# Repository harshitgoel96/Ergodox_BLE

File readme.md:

# There is no active development on this keyboard. Feel free to do whatever you want. I have moved to Pteron36.
The PCB is in working statue, but no further support or development will be done on this project.
------------------------------------------------------------------------------------------------------------------------------------------
Ergodox BLE
===========

I love my [Ergodox](https://i.imgur.com/aIGm8G6h.jpg) , but it is not Bluetooth. I recently got to know about Bluemicro from u/jpconstantineau which is replacement for pro micro with BLE built in, and I also got to know about Proton C, which has USB C connector and is built for QMK. The original Ergodox uses Tinsy and Ergodone uses pro micro. Both the PCBs don't have support for either of the MCU directly and so I got to work and redid the PCB and I came up with this.

This is my first attempt at making a PCB and I need help from PCB hardware experts if everything is ok or do I need make some changes.

The Ergodox Keyboard was originally developed by “Dox” (Dominic Beauchamp). 

------------------------------------------------------------------------------------------------------------------------------------------
There has ben lot of progress, the complete timeline of the project is available in [Project update](./project_udpate.md) file

First prototype assembled

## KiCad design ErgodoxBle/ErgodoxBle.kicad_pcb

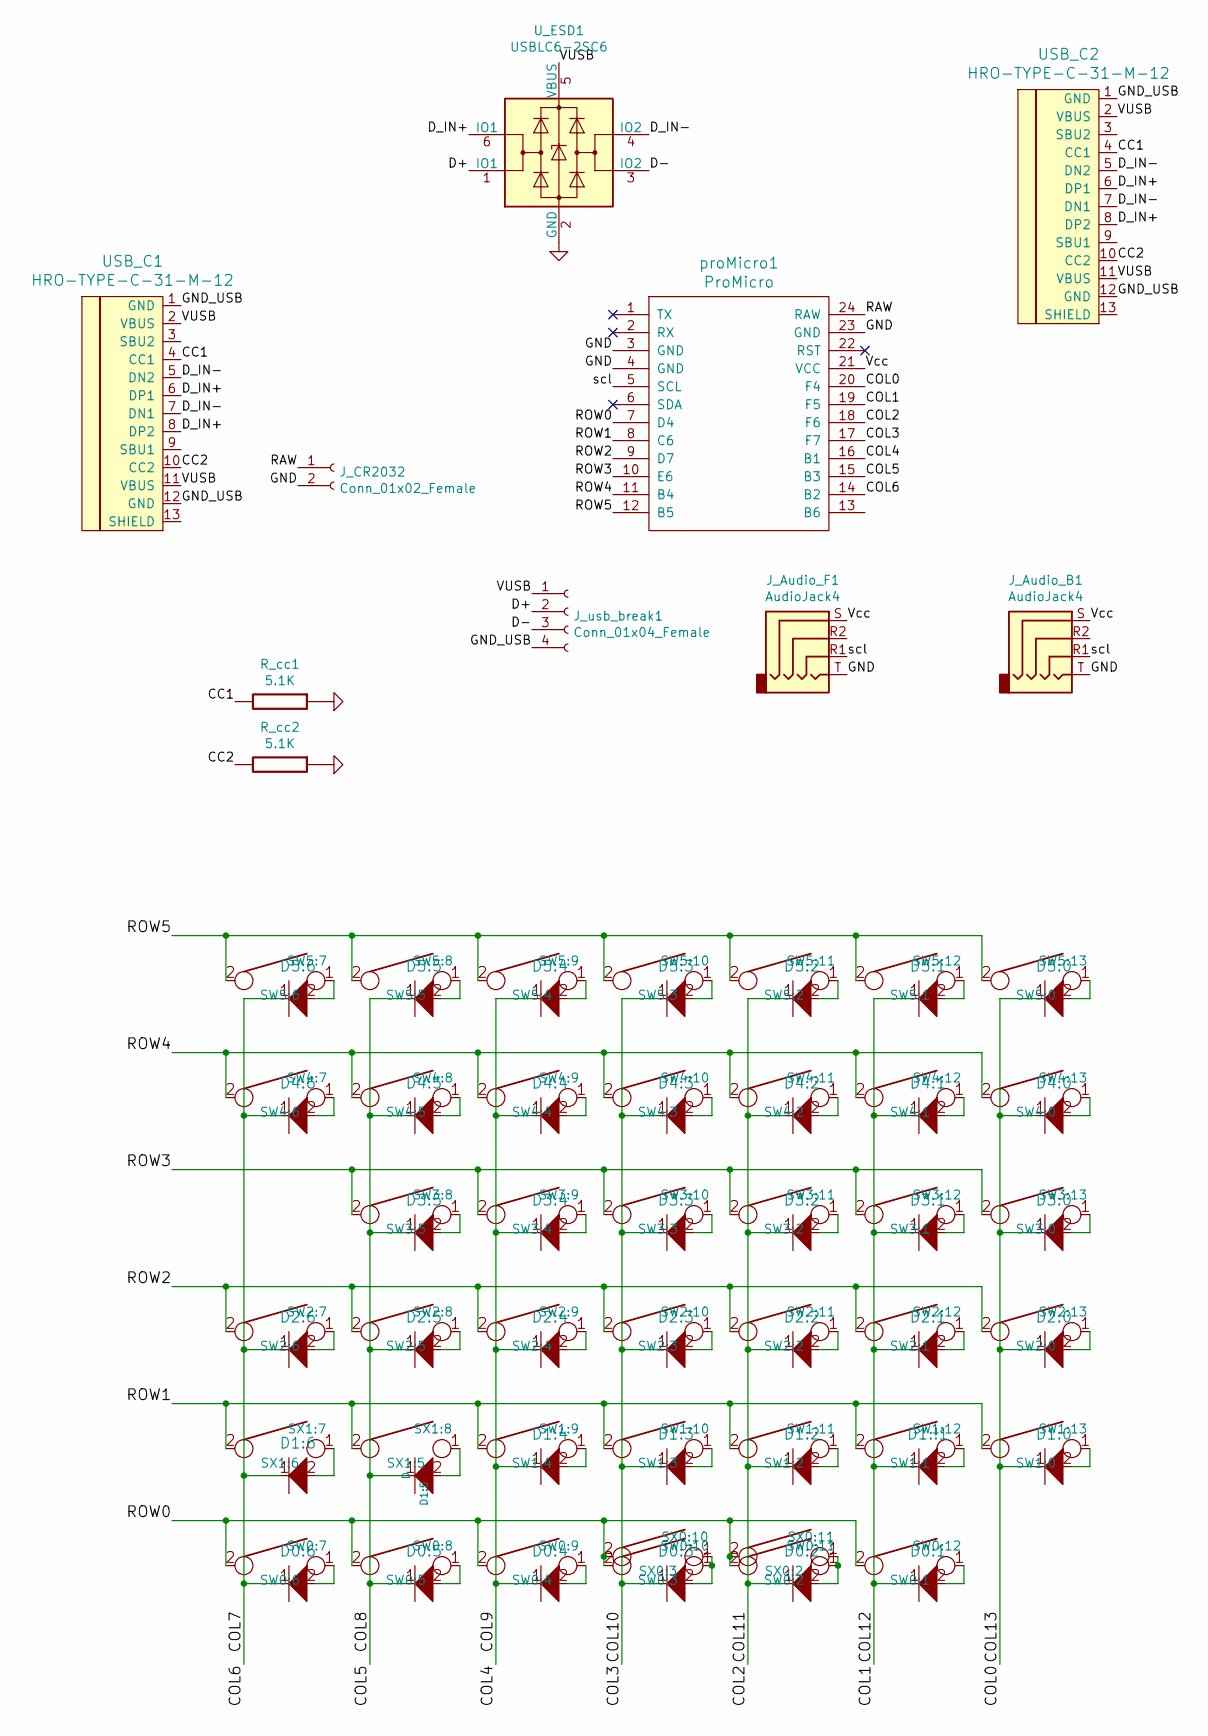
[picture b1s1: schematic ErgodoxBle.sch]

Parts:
D0:1, D0:2, D0:3, D0:4, D0:5, D0:6, D1:0, D1:2, D1:3, D1:4, D1:5, D1:6, D1:!1, D2:0, D2:1, D2:2, D2:3, D2:4, D2:5, D2:6, D3:0, D3:1, D3:2, D3:3, D3:4, D3:5, D4:0, D4:1, D4:2, D4:3, D4:4, D4:5, D4:6, D5:0, D5:1, D5:2, D5:3, D5:4, D5:5, D5:6: D; Diode-dual
J_Audio_B1: AudioJack4; Jack_3.5mm_PJ320D_Horizontal
J_Audio_F1: AudioJack4; Jack_3.5mm_PJ320D_Horizontal
J_CR2032: Conn_01x02_Female; Custom_SolderWirePad_1x02_P1.75mm_Drill1.09mm
J_usb_break1: Conn_01x04_Female; Custom_SolderWirePad_1x04_P1.7526mm_Drill1.0922mm
R_cc1, R_cc2: 5.1K; Resistor-Hybrid
SW0:7: SW0:6; Hybrid_PCB_100H_Dual_hole
SW0:8: SW0:5; Hybrid_PCB_100H_Dual_hole
SW0:9: SW0:4; Hybrid_PCB_100H_Dual_hole
SW0:10: SW0:3; Hybrid_PCB_200H-dual
SW0:11: SW0:2; Hybrid_PCB_200H-dual
SW0:12: SW0:1; Hybrid_PCB_100H_Dual_hole
SW1:9: SW1:4; Hybrid_PCB_100H_Dual_hole
SW1:10: SW1:3; Hybrid_PCB_100H_Dual_hole
SW1:11: SW1:2; Hybrid_PCB_100H_Dual_hole
SW1:12: SW1:1; Hybrid_PCB_100H_Dual_hole
SW1:13: SW1:0; Hybrid_PCB_100H_Dual_hole
SW2:7: SW2:6; Hybrid_PCB_100H_Dual_hole
SW2:8: SW2:5; Hybrid_PCB_100H_Dual_hole
SW2:9: SW2:4; Hybrid_PCB_100H_Dual_hole
SW2:10: SW2:3; Hybrid_PCB_100H_Dual_hole
SW2:11: SW2:2; Hybrid_PCB_100H_Dual_hole
SW2:12: SW2:1; Hybrid_PCB_100H_Dual_hole
SW2:13: SW2:0; correct_Hybrid_PCB_100v_150H_Dual_hole
SW3:8: SW3:5; Hybrid_PCB_100H_Dual_hole
SW3:9: SW3:4; Hybrid_PCB_100H_Dual_hole
SW3:10: SW3:3; Hybrid_PCB_100H_Dual_hole
SW3:11: SW3:2; Hybrid_PCB_100H_Dual_hole
SW3:12: SW3:1; Hybrid_PCB_100H_Dual_hole
SW3:13: SW3:0; correct_Hybrid_PCB_100v_150H_Dual_hole
SW4:7: SW4:6; Hybrid_PCB_100H_Dual_hole
SW4:8: SW4:5; Hybrid_PCB_100H_Dual_hole
SW4:9: SW4:4; Hybrid_PCB_100H_Dual_hole
SW4:10: SW4:3; Hybrid_PCB_100H_Dual_hole
SW4:11: SW4:2; Hybrid_PCB_100H_Dual_hole
SW4:12: SW4:1; Hybrid_PCB_100H_Dual_hole
SW4:13: SW4:0; correct_Hybrid_PCB_100v_150H_Dual_hole
SW5:7: SW5:6; Hybrid_PCB_100H_Dual_hole
SW5:8: SW5:5; Hybrid_PCB_100H_Dual_hole
SW5:9: SW5:4; Hybrid_PCB_100H_Dual_hole
SW5:10: SW5:3; Hybrid_PCB_100H_Dual_hole
SW5:11: SW5:2; Hybrid_PCB_100H_Dual_hole
SW5:12: SW5:1; Hybrid_PCB_100H_Dual_hole
SW5:13: SW5:0; correct_Hybrid_PCB_100v_150H_Dual_hole
SX0:10: SX0:3; Hybrid_PCB_100H_Dual_hole
SX0:11: SX0:2; Hybrid_PCB_100H_Dual_hole
SX1:7: SX1:6; Hybrid_PCB_100H_Dual_hole
SX1:8: SX1:5; Hybrid_PCB_100H_Dual_hole
USB_C1, USB_C2: HRO-TYPE-C-31-M-12
U_ESD1: USBLC6-2SC6; SOT-23-6
proMicro1: ProMicro; ArduinoProMicro

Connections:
/CC1: R_cc1.2, USB_C1.4 (CC1), USB_C2.4 (CC1)
/CC2: R_cc2.2, USB_C1.10 (CC2), USB_C2.10 (CC2)
/COL0: D1:0.1, D2:0.1, D3:0.1, D4:0.1, D5:0.1, proMicro1.20 (F4)
/COL1: D0:1.1, D1:!1.1, D2:1.1, D3:1.1, D4:1.1, D5:1.1, proMicro1.19 (F5)
/COL4: D0:4.1, D1:4.1, D2:4.1, D3:4.1, D4:4.1, D5:4.1, proMicro1.16 (B1)
/COL5: D0:5.1, D1:5.1, D2:5.1, D3:5.1, D4:5.1, D5:5.1, proMicro1.15 (B3)
/COL6: D0:6.1, D1:6.1, D2:6.1, D4:6.1, D5:6.1, proMicro1.14 (B2)
/COL10: D0:3.1, D1:3.1, D2:3.1, D3:3.1, D4:3.1, D5:3.1, proMicro1.17 (F7)
/COL11: D0:2.1, D1:2.1, D2:2.1, D3:2.1, D4:2.1, D5:2.1, proMicro1.18 (F6)
/D+: J_usb_break1.2, U_ESD1.1 (IO1)
/D-: J_usb_break1.3, U_ESD1.3 (IO2)
/D_IN+: USB_C1.6 (DP1), USB_C1.8 (DP2), USB_C2.6 (DP1), USB_C2.8 (DP2), U_ESD1.6 (IO1)
/D_IN-: USB_C1.5 (DN2), USB_C1.7 (DN1), USB_C2.5 (DN2), USB_C2.7 (DN1), U_ESD1.4 (IO2)
/GND_USB: J_usb_break1.4, USB_C1.1 (GND), USB_C1.12 (GND), USB_C2.1 (GND), USB_C2.12 (GND)
/RAW: J_CR2032.1, proMicro1.24 (RAW)
/ROW0: SW0:7.2, SW0:8.2, SW0:9.2, SW0:10.2, SW0:11.2, SW0:12.2, SX0:10.2, SX0:11.2, proMicro1.7 (D4)
/ROW1: SW1:9.2, SW1:10.2, SW1:11.2, SW1:12.2, SW1:13.2, SX1:7.2, SX1:8.2, proMicro1.8 (C6)
/ROW2: SW2:7.2, SW2:8.2, SW2:9.2, SW2:10.2, SW2:11.2, SW2:12.2, SW2:13.2, proMicro1.9 (D7)
/ROW3: SW3:8.2, SW3:9.2, SW3:10.2, SW3:11.2, SW3:12.2, SW3:13.2, proMicro1.10 (E6)
/ROW4: SW4:7.2, SW4:8.2, SW4:9.2, SW4:10.2, SW4:11.2, SW4:12.2, SW4:13.2, proMicro1.11 (B4)
/ROW5: SW5:7.2, SW5:8.2, SW5:9.2, SW5:10.2, SW5:11.2, SW5:12.2, SW5:13.2, proMicro1.12 (B5)
/VUSB: J_usb_break1.1, USB_C1.2 (VBUS), USB_C1.11 (VBUS), USB_C2.2 (VBUS), USB_C2.11 (VBUS), U_ESD1.5 (VBUS)
/Vcc: J_Audio_B1.S, J_Audio_F1.S, proMicro1.21 (VCC)
/scl: J_Audio_B1.R1, J_Audio_F1.R1, proMicro1.5 (SCL)
GND: J_Audio_B1.T, J_Audio_F1.T, J_CR2032.2, R_cc1.1, R_cc2.1, U_ESD1.2 (GND), proMicro1.3 (GND), proMicro1.4 (GND), proMicro1.23 (GND)
unnamed: D0:1.2, SW0:12.1
unnamed: D0:2.2, SW0:11.1, SX0:11.1
unnamed: D0:3.2, SW0:10.1, SX0:10.1
unnamed: D0:4.2, SW0:9.1
unnamed: D0:5.2, SW0:8.1
unnamed: D0:6.2, SW0:7.1
unnamed: D1:0.2, SW1:13.1
unnamed: D1:2.2, SW1:11.1
unnamed: D1:3.2, SW1:10.1
unnamed: D1:4.2, SW1:9.1
unnamed: D1:5.2, SX1:8.1
unnamed: D1:6.2, SX1:7.1
unnamed: D1:!1.2, SW1:12.1
unnamed: D2:0.2, SW2:13.1
unnamed: D2:1.2, SW2:12.1
unnamed: D2:2.2, SW2:11.1
unnamed: D2:3.2, SW2:10.1
unnamed: D2:4.2, SW2:9.1
unnamed: D2:5.2, SW2:8.1
unnamed: D2:6.2, SW2:7.1
unnamed: D3:0.2, SW3:13.1
unnamed: D3:1.2, SW3:12.1
unnamed: D3:2.2, SW3:11.1
unnamed: D3:3.2, SW3:10.1
unnamed: D3:4.2, SW3:9.1
unnamed: D3:5.2, SW3:8.1
unnamed: D4:0.2, SW4:13.1
unnamed: D4:1.2, SW4:12.1
unnamed: D4:2.2, SW4:11.1
unnamed: D4:3.2, SW4:10.1
unnamed: D4:4.2, SW4:9.1
unnamed: D4:5.2, SW4:8.1
unnamed: D4:6.2, SW4:7.1
unnamed: D5:0.2, SW5:13.1
unnamed: D5:1.2, SW5:12.1
unnamed: D5:2.2, SW5:11.1
unnamed: D5:3.2, SW5:10.1
unnamed: D5:4.2, SW5:9.1
unnamed: D5:5.2, SW5:8.1
unnamed: D5:6.2, SW5:7.1

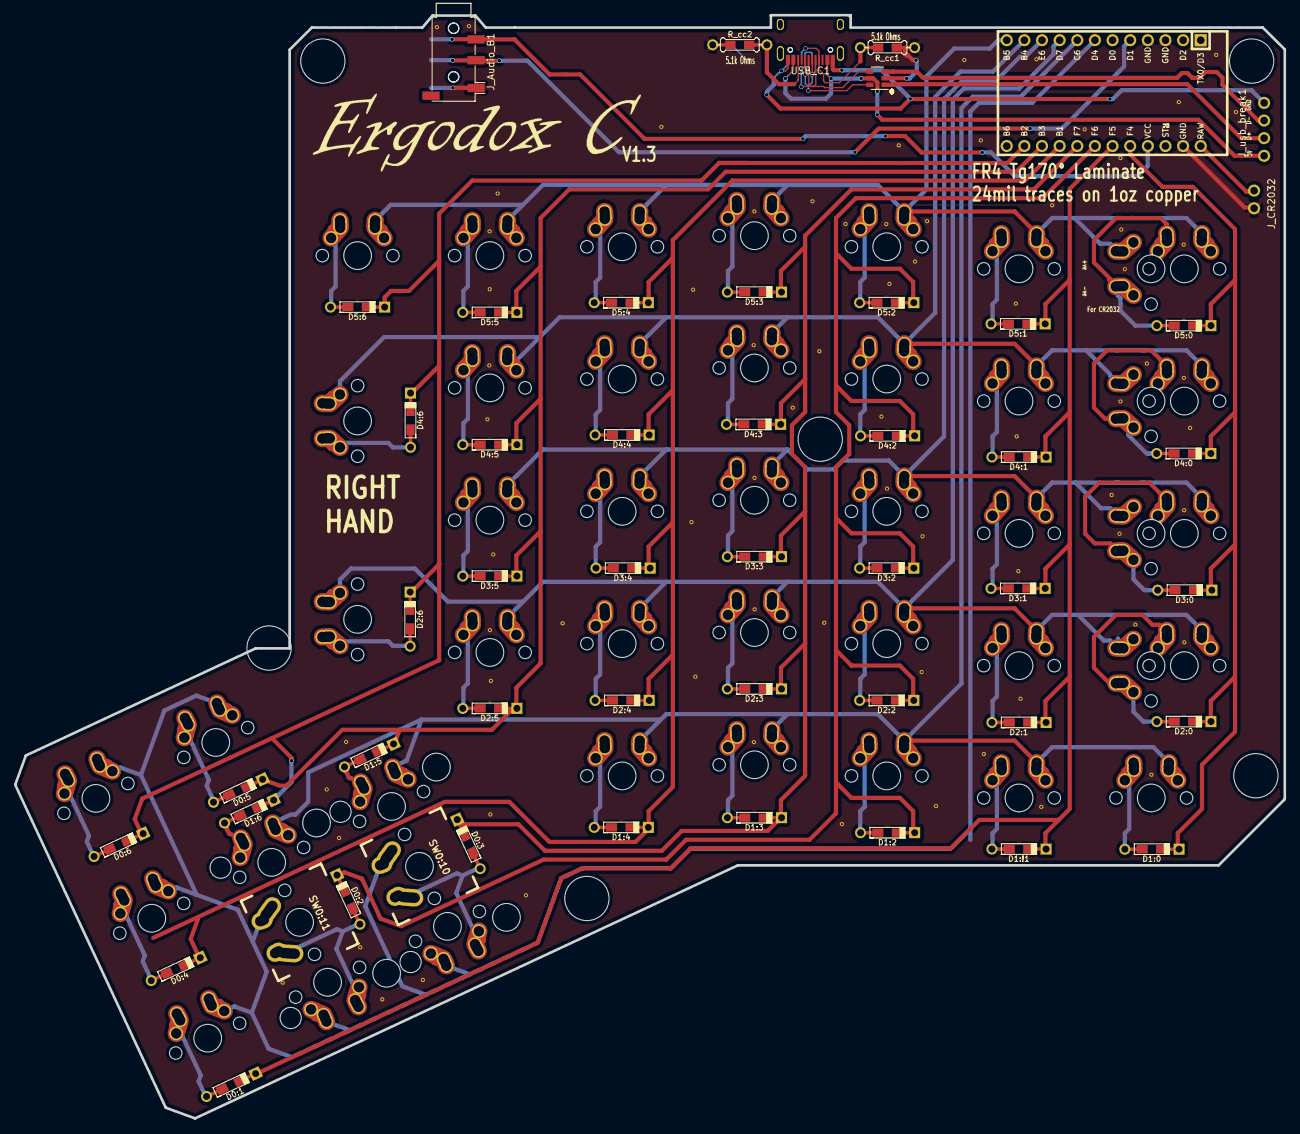
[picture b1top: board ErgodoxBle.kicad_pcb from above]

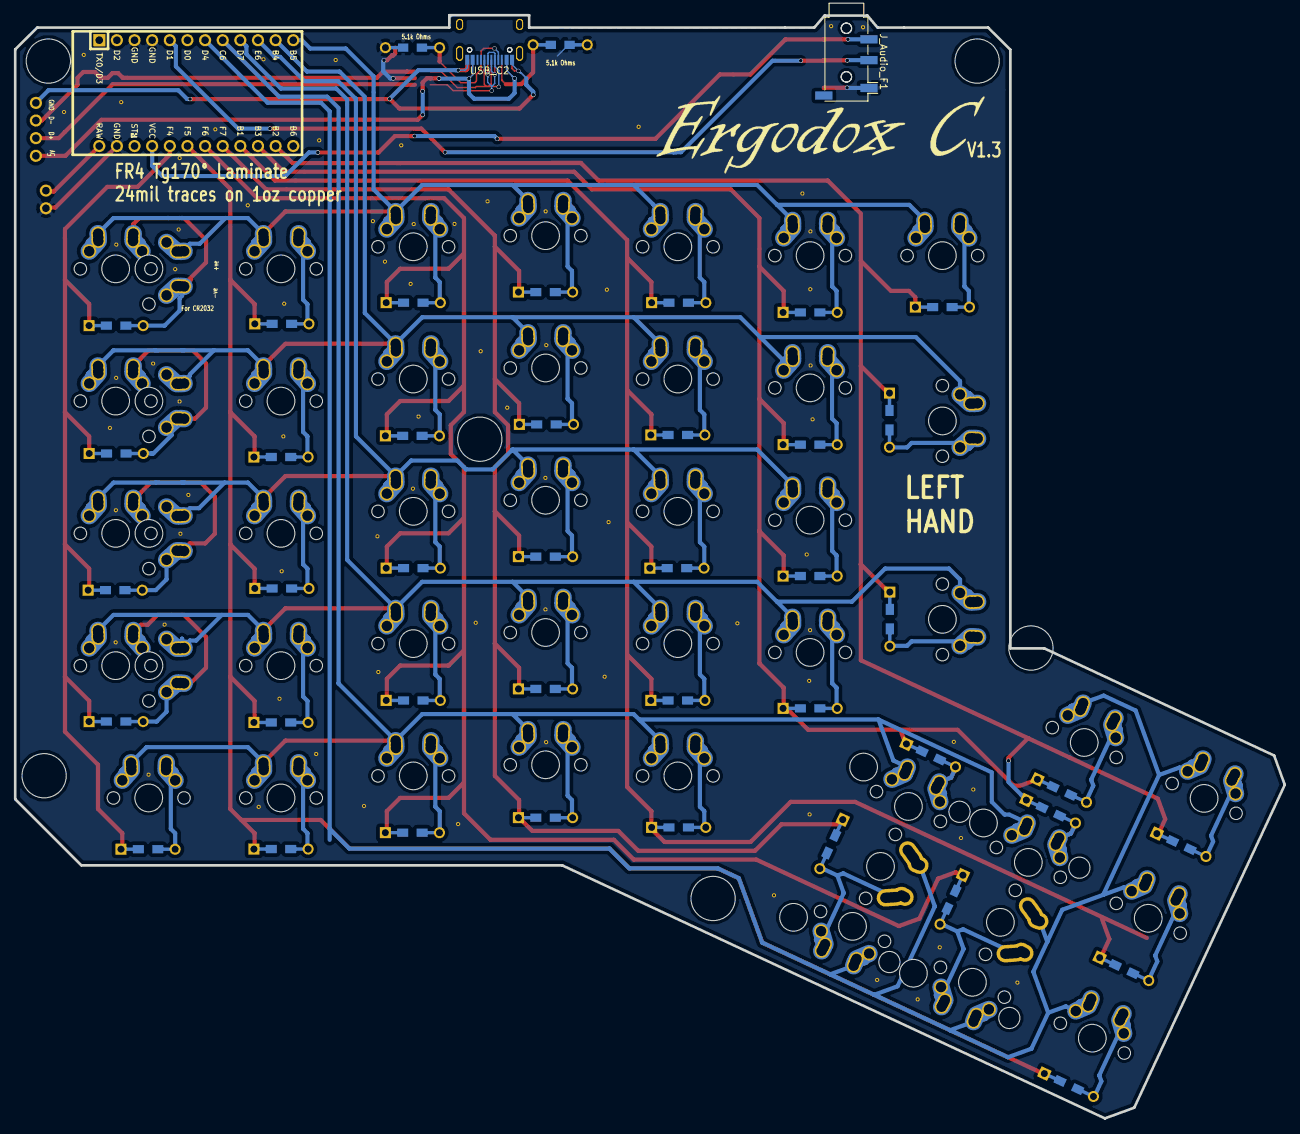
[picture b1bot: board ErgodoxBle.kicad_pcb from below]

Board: 2 copper layers, 182.8 x 158.9 mm, 92 parts (2 on the bottom side), 65 nets.

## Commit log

2019-01-20 finish prototype
2019-01-20 use correct switch footprint
2019-01-20 generate gerber files for inspection
2019-01-20 align the pcb with ergodone case
2019-01-20 updated gerber files
2019-01-20 add solder jumpber on both layers
2019-01-20 added clearence for ProtonC
2019-01-20 remove obsolete gerber files
2019-01-20 gerber updated
2019-01-21 added readme and GPL license
2019-01-21 fix grammer
    updated text to clearer text
2019-01-21 Redo the existing ergodox pcb
2019-01-22 Added USB-C
2019-01-22 finalize pcb
2019-01-23 schema and pcb pdf
2019-01-23 updated USB-C pad and added zone filled pdf
2019-01-26 add project time line
2019-01-26 update project timeline
2019-01-30 case added
2019-01-30 update entry for case
2019-01-31 add dxf version
2019-03-24 update what has happened in last two months
2019-03-24 add todo
2019-03-25 updated progress
2019-03-28 project updates for 29 March
2019-03-28 update read me.
2019-03-28 corrected formatting
2019-03-28 corrected image link
2019-03-28 update pcb, removed unwanted i2c wire, will go only serial over sda
2019-03-29 Added pad for CR2032 module for bluemicro
2019-04-27 v 1.3, almost the final version
2019-04-29 final version before hardware testing
2019-05-01 minor changes
2019-05-01 final release
2019-05-01 update case design to allow M3 round standoff, 5mm OD, 3mm ID
2019-05-01 updated project timeline and todo
2019-05-02 align front and back usb c port
2019-05-02 redo fill zone
2019-05-02 add plate for alps switch
2019-05-02 remove obsolete file
2019-05-02 update project update file
2019-06-09 added svg for case
